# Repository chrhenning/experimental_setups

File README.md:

# Conducting sophisticated Fear Conditioning, Active Avoidance and other Experiments with a Single Software 

This repository is meant to control fear conditioning (FC), active avoidance (AA) or other experimental setups. The software was developed in the lab of [Benjamin Grewe](https://www.ini.uzh.ch/people/bgrewe). The code allows a simple way to design and run complex real-time experiments and record for multiple subjects in parallel; all controlled and aligned with a single computer. It also contains an expressive evaluation pipeline for FC experiments to automatically evaluate the outcome of an experiment once the data is acquired.

## Installation

The software is developed in Matlab (tested with Matlab R2017b). It makes use of several toolboxes, such as the [Image Acquisition Toolbox](https://ch.mathworks.com/products/imaq.html) and the [Data Acquisition Toolbox](https://ch.mathworks.com/products/daq.html).

Before running the programs, make sure that all the **required libraries** are downloaded and stored in the folder [lib](lib). A list of all required libraries and their download links are provided in the [lib](lib) folder.

## Documentation

More documentation is provided in the folder [docs](docs). The code is well documented and should be straight-forward to use by users, that are familiar with Matlab. After reading the documentation, one should start by exploring the repository (just opening files and reading their docstrings). Additional documentation can be requested from <henningc@ethz.ch>.

## Experimental Setup

In this section, we briefly describe the experimental setup for which the software was designed and tested. More extensive documentation can be requested from <henningc@ethz.ch>.

Most importantly, the software expects a data acquisition solution from [NI](http://www.ni.com/data-acquisition/) (NIDAQ). Such a NIDAQ board essentially controls all the stimuli presented to the subjects during an experiment.

The software also allows an easy recording of the behavior expressed by the subjects, by using one or multiple *behavior cameras*. Currently, the setup has been tested with two camera types: [Allied Vision Guppy PRO F125B](https://www.alliedvision.com/en/products/cameras/detail/Guppy%20PRO/F-125.html) and [ImagingSource DMK 23FV024](https://www.theimagingsource.com/products/industrial-cameras/firewire-800-monochrome/dmk23fv024/). Both are used as behavior cameras in our setups.

For both setups, we use foot shockers and test cages from [Coulbourn](https://www.coulbourn.com). However, this is in principle arbitrary. For the AA setup, we needed to develop a dedicated piece of hardware, in order to react in realtime. Though, this hardware should be general enough to adapt to other scenarios as it is fully programmable.

## Terminology

To control a complex experiment, one has to generate a design file, that adheres a certain format. In connection to this design file, there are many terms that are used throughout the repository, that are essential to understand in order to use the code. A design file distinguishes between *cohorts*, *groups*, *sessions* and *subjects*. A tuple of (*cohort*, *group*, *session*, *subject*) uniquely identifies a *recording*.

For instance, *subject* 2 in *session* 3 from *cohort* 1, *group* 2 specifies a single *recording*, i.e., the design files fully defines what stimuli are presented and when and how long the behavior is going to be recorded. 

## Repository Structure

This is a list of folders belonging to the repository and their main purpose.
* **control**: Contains the code to control the setup.
* **evaluation**: Contains the evaluation pipeline for an experiment.
* **experiments**: Contains example experiments conducted with the software (most importantly, their *design file generation* scripts).
* **lib**: External libraries.
* **misc**: Several useful tools (e.g., video postprocessing).

We now provide a detailed explanation for some of the above folders.

### Control

The setup is controlled by the [run_experiment](control/run_experiment.m) script in the folder [control](control). The control software provides a user-friendly way to conduct an experiment. Its focus lays on **ensuring the correct timing of all stimuli, such that they can be precisely aligned with neural recordings**.

An experiment is configured via [params.m](control/params.m) in the same folder. Recordings can either be controlled by a design file or generated ad-hoc (note, automatically generated design files only allow very simplistic designs).

Here is a short summary of the main features currently implemented (June 24th, 2018):
* Capability to run multiple recordings in parallel
* Direct control of behavior cameras including camera preview
* Ad-hoc design generation
* Recordings can be run in NIDAQ continuous mode
* Sounds can be played via the NIDAQ board or via the soundcard (in which case one can record them to correct timing afterwards)
* Recordings can be started via an external trigger
* Arbitrary trigger signals can be generated
* Sessions can be paused and terminated

### Experiments
All experiment related scripts should be in the folder [experiments](experiments). The subfolders contain code specific to an experiment, including how to generate the design file. Note, that some experiments may use outdated design file formats. One can always check the design file format via the script [check_design_file](misc/experiment_design/check_design_file.m). In the folder [experiments/examples](experiments/examples) are examples specifically designed to make new users familiar with the design file programming. 

### Evaluation
Preliminary evaluation scripts are available in the folder [evaluation](evaluation). **Note**, we currently provide only code for FC experiments. The provided evaluation pipeline only looks at the animals behavior.

The evaluation code requires that freezing traces have been extracted beforehand. The freezing detection software is currently hosted in another repository *FreezingDetection*. To get access to our freezing detection pipeline, please contact <henningc@ethz.ch> or <behret@ethz.ch>.

### Misc

This folder contains a collection of useful scripts. To name just a few:
* `misc/active_avoidance`: Specifications and example implementations of the hardware designed to allow active designs.
* `misc/behavior_cameras/postprocessing`: A tool to postprocess behavior videos (e.g., compress them).
* `misc/behavior_cameras/annotation`: Annotate behavior videos with events from the design file (only supports FC experiments).
* `misc/experiment_design/check_design_file.m`: A script to check whether a design file adheres the correct format.
* `misc/measure_soundlevel`: A tool to measure the sound pressure level (SPL) via a computer soundcard using speakers and microphone.
* `misc/sound_generation`: Scripts to generate or play tones (can be used to adjust SPL of speakers).

## Design File

The design file is one of the most important aspects, as it completely defines the experimental design. It therefore is used to control the setup and to control the evaluation.

The design file itself is a file named `experiment.mat`, that contains a variable `experiment`.

The design file is the only piece that a user has to contribute to control its experiment with this software collection. It adheres a certain format that can be checked via the script [check_design_file](misc/experiment_design/check_design_file.m).

The design file is contained in the design folder (which may incorparate other files that are referenced in the design file via relative paths (e.g., sound files)). The experiment is designed in a tree structure (where edges may be multi-edges). The first level are *cohorts*, which themselves split into *groups* (one may also think of groups and subgroups). These are divided into *sessions*, which are split into *subjects*.

Please run the script [experiments/examples/fear_conditioning/generate_fc_design_file.m](experiments/examples/fear_conditioning/generate_fc_design_file.m) to generate an example design folder. The script expects an output folder name as argument. Please explore the resulting `experiment.mat` file (it also generates a JSON file with the same content, in case this is easier to read).

A detailed explanantion of design file format can be found in the [docs](docs) folder.

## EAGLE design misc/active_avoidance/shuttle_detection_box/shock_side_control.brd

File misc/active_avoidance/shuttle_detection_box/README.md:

# Shuttle Detection Box

The *shuttle detection box* is a programmable hardware device, that is used to detect mouse shuttling in almost realtime and react appropriately.

## Why is this extra Hardware necessary?

Since we already have the NIDAQ Board for realtime-processing, we shouldn't need another device. However, the NIDAQ requires predefined signals and allows no processing of incoming data in realtime. Processing has to be done via callback functions, such that the reaction depends on the OS scheduling. Therefore, we integrate and process incoming information via this device and act immediately upon shuttling detection.

## Typical scenario

The heart of the box is an Arduino Nano, that integrates all the information. It can receive the position (cage side) of the subject either via USB from the computer (using online camera tracking) or directly via BNC connectors (e.g., from photodetectors). If currently a trial is presented to the subject (e.g., tone followed by a shock) the computer sets a control input via the NIDAQ board. If a shuttling appears during this trial, the *shuttle detection box* will react, e.g., via blocking signals from the computer (sound and shock commands).

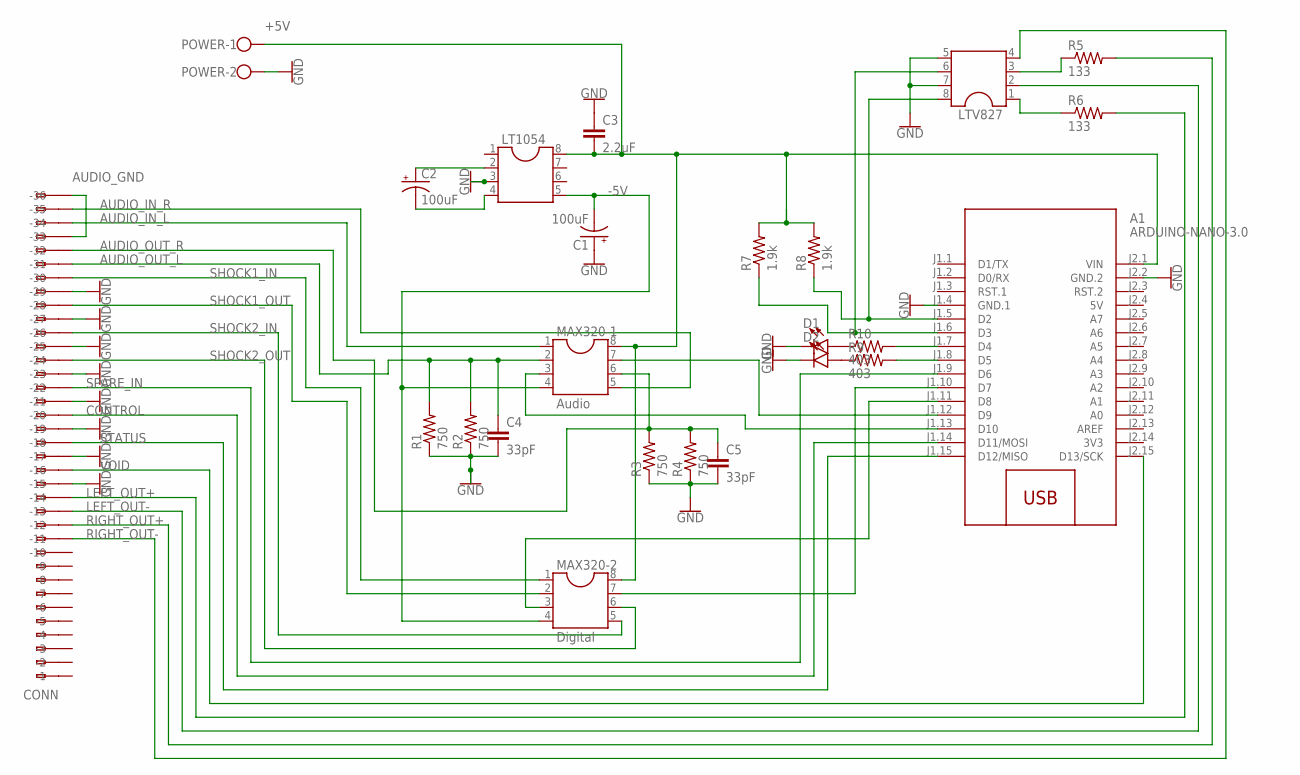
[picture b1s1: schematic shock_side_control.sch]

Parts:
A1: ARDUINO-NANO-3.0
C1, C2: 100uF; CPOL-RADIAL-2.5MM-6.5MM
C3: 2.2uF; C5B2.5
C4, C5: 33pF; C5B2.5
CONN: 233-136
D1, D2: LED-3MM-NO_SILK; LED_3MM-NS
LT1054: DIL8; DIL08
LTV827: DIL8; DIL08
MAX320-1: Audio; DIL08
MAX320-2: Digital; DIL08
POWER: W237-02P; W237-132
R1, R2, R3, R4: 750; 0805-THM
R5, R6: 133; 0805-THM
R7, R8: 1.9k; 0805-THM
R9, R10: 403; 0805-THM

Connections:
3V3: A1.J2.14 (3V3)
5V: A1.J2.4 (5V)
+5V: A1.J2.1 (VIN), C3.2, LT1054.8, MAX320-1.8, MAX320-2.8, POWER.1, R7.2, R8.2
-5V: C1.2 (-), LT1054.5, MAX320-1.4, MAX320-2.4
AUDIO_GND: CONN.A33 (-33), CONN.A36 (-36)
AUDIO_IN_L: CONN.A34 (-34), MAX320-1.1
AUDIO_IN_R: CONN.A35 (-35), MAX320-1.5
AUDIO_OUT_L: C4.1, CONN.A31 (-31), MAX320-1.2, R1.2, R2.2
AUDIO_OUT_R: C5.1, CONN.A32 (-32), MAX320-1.6, R3.2, R4.2
CONTROL: A1.J1.14 (D11/MOSI), CONN.A20 (-20)
GND: A1.J1.4 (GND.1), A1.J2.2 (GND.2), C1.1 (+), C3.1, C4.2, C5.2, CONN.A15 (-15), CONN.A17 (-17), CONN.A19 (-19), CONN.A21 (-21), CONN.A23 (-23), CONN.A25 (-25), CONN.A27 (-27), CONN.A29 (-29), D1.K (C), D2.K (C), LT1054.3, LTV827.5, LTV827.7, POWER.2, R1.1, R2.1, R3.1, R4.1
LEFT_OUT+: CONN.A14 (-14), R6.2
LEFT_OUT-: CONN.A13 (-13), LTV827.2
unnamed: A1.J1.12 (D9), MAX320-1.7
unnamed: C2.2 (-), LT1054.4
unnamed: C2.1 (+), LT1054.2
unnamed: A1.J1.13 (D10), MAX320-1.3
unnamed: D2.A, R9.1
unnamed: D1.A, R10.1
unnamed: A1.J1.8 (D5), R9.2
unnamed: A1.J1.7 (D4), R10.2
unnamed: A1.J1.10 (D7), MAX320-2.7
unnamed: A1.J1.11 (D8), MAX320-2.3
unnamed: LTV827.1, R6.1
unnamed: LTV827.3, R5.1
unnamed: A1.J1.5 (D2), LTV827.8, R8.1
unnamed: A1.J1.6 (D3), LTV827.6, R7.1
RIGHT_OUT+: CONN.A12 (-12), R5.2
RIGHT_OUT-: CONN.A11 (-11), LTV827.4
SHOCK1_IN: CONN.A30 (-30), MAX320-2.1
SHOCK1_OUT: CONN.A28 (-28), MAX320-2.2
SHOCK2_IN: CONN.A26 (-26), MAX320-2.5
SHOCK2_OUT: CONN.A24 (-24), MAX320-2.6
SPARE_IN: A1.J1.9 (D6), CONN.A22 (-22)
STATUS: A1.J1.15 (D12/MISO), CONN.A18 (-18)
VOID: A1.J2.15 (D13/SCK), CONN.A16 (-16)

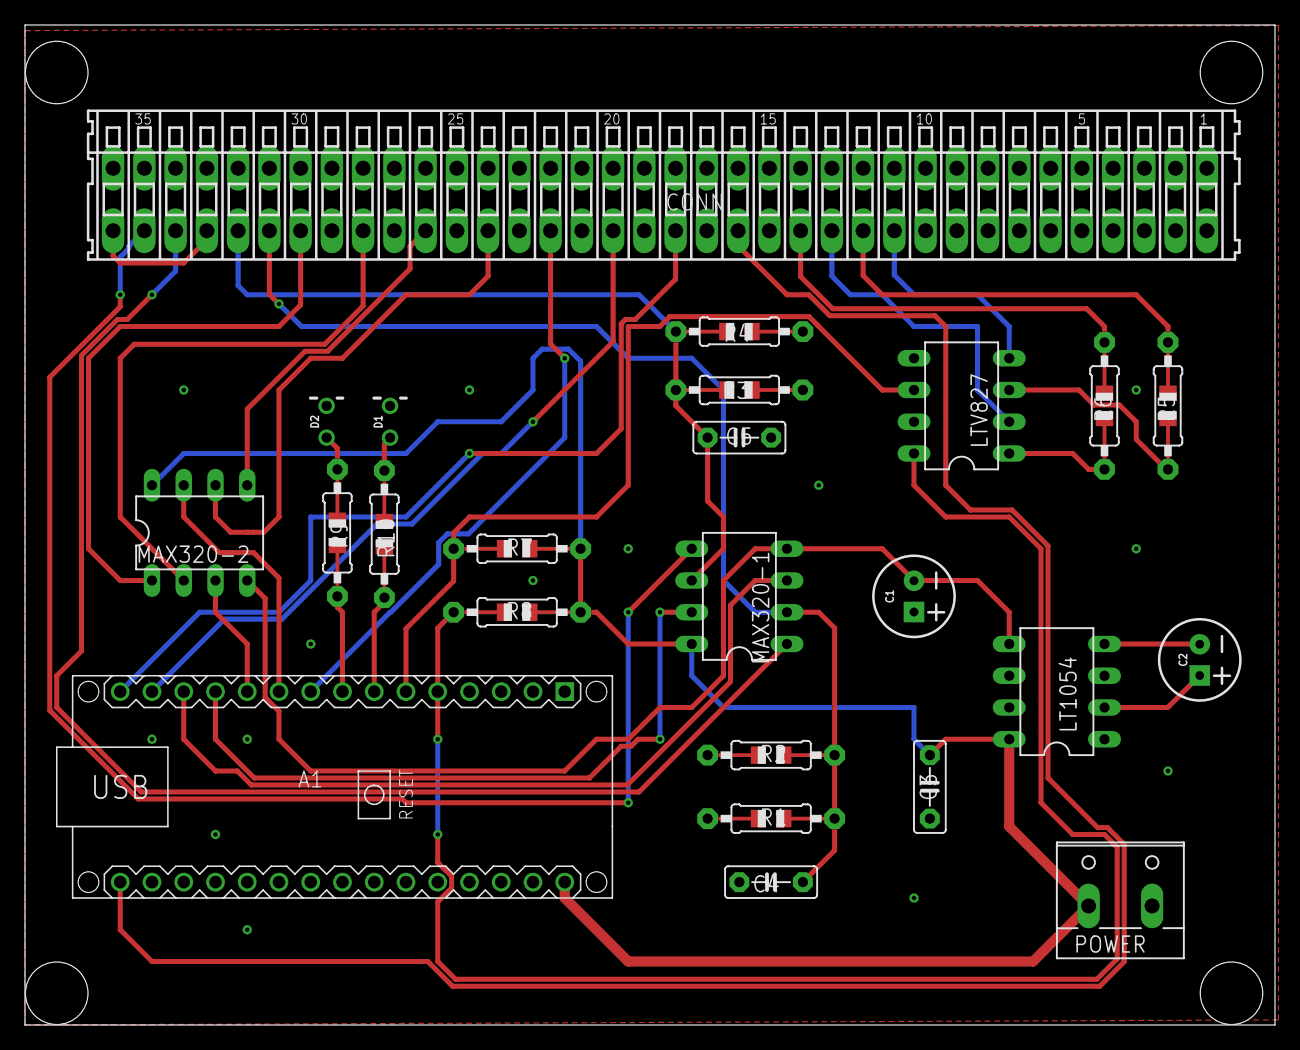
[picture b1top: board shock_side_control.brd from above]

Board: 2 copper layers, 100.0 x 80.0 mm, 24 parts (0 on the bottom side), 34 nets.

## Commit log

2018-08-24 Pushing first public version to the repo.
2019-01-06 The GUI during an experiment was refurbished and improved. Two major features were added: the possibility to pause and stop a recording. The code has been extensively tested in our lab over several m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
2019-01-07 Update README.md
    Fixed Typo
2019-01-27 Update run_experiment.m
    Fixed typo.
2019-01-27 Update take_reference_frame.m
    Fixed typo.

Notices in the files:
parts and their libraries:
SparkFun-Capacitors: Licensing: Creative Commons ShareAlike 4.0 International - https://creativecommons.org/licenses/by-sa/4.0
diy-modules: Released under the Creative Commons Attribution 4.0 International License: http://creativecommons.org/licenses/by/4.0
